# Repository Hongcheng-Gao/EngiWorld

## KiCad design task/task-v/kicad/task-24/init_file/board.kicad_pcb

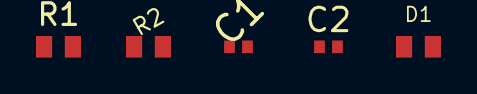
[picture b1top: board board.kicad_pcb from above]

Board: 2 copper layers, 6 parts (0 on the bottom side), 4 nets, no tracks yet.

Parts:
C1: 100nF; C_0402_1005Metric
C2: 10uF; C_0402_1005Metric
D1: LED_RED; LED_0603_1608Metric
Q1: MMBT3904; SOT-23
R1: 10k; R_0603_1608Metric
R2: 4k7; R_0603_1608Metric

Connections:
GND: C1.2, C2.2, D1.1, Q1.1, R1.2
SIG_A: C2.1, R2.2
SIG_B: D1.2, Q1.2
VCC: C1.1, Q1.3, R1.1, R2.1
